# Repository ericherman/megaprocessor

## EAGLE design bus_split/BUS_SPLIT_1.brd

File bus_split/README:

Data bus breakout.

This is just used for generating constant values.

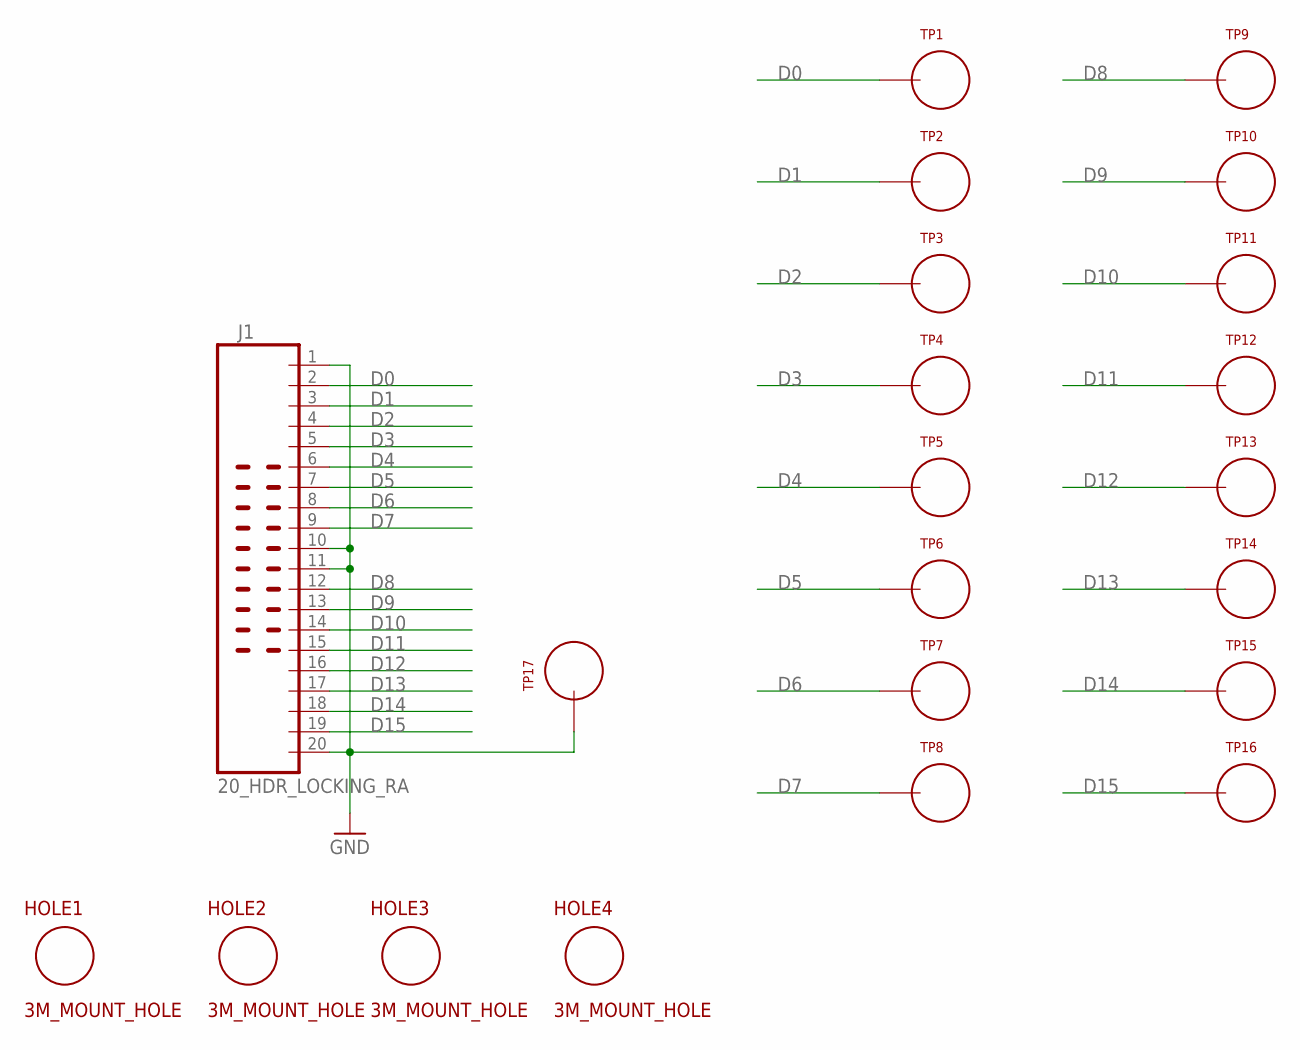
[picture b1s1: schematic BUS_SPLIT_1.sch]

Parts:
HOLE1, HOLE2, HOLE3, HOLE4: 3M_MOUNT_HOLE; 3M_HOLE
J1: 20_HDR_LOCKING_RA
TP1, TP2, TP3, TP4, TP5, TP6, TP7, TP8, TP9, TP10, TP11, TP12, TP13, TP14, TP15, TP16, TP17: TEST_LOOP

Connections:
D0: J1.2, TP1.P$1
D1: J1.3, TP2.P$1
D2: J1.4, TP3.P$1
D3: J1.5, TP4.P$1
D4: J1.6, TP5.P$1
D5: J1.7, TP6.P$1
D6: J1.8, TP7.P$1
D7: J1.9, TP8.P$1
D8: J1.12, TP9.P$1
D9: J1.13, TP10.P$1
D10: J1.14, TP11.P$1
D11: J1.15, TP12.P$1
D12: J1.16, TP13.P$1
D13: J1.17, TP14.P$1
D14: J1.18, TP15.P$1
D15: J1.19, TP16.P$1
GND: J1.1, J1.10, J1.11, J1.20, TP17.P$1

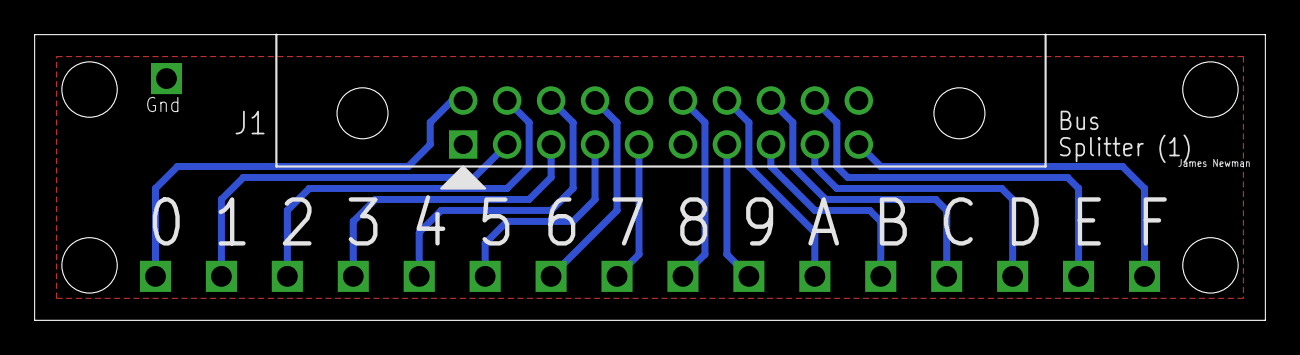
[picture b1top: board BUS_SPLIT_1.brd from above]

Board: 2 copper layers, 71.1 x 16.5 mm, 22 parts (0 on the bottom side), 17 nets.

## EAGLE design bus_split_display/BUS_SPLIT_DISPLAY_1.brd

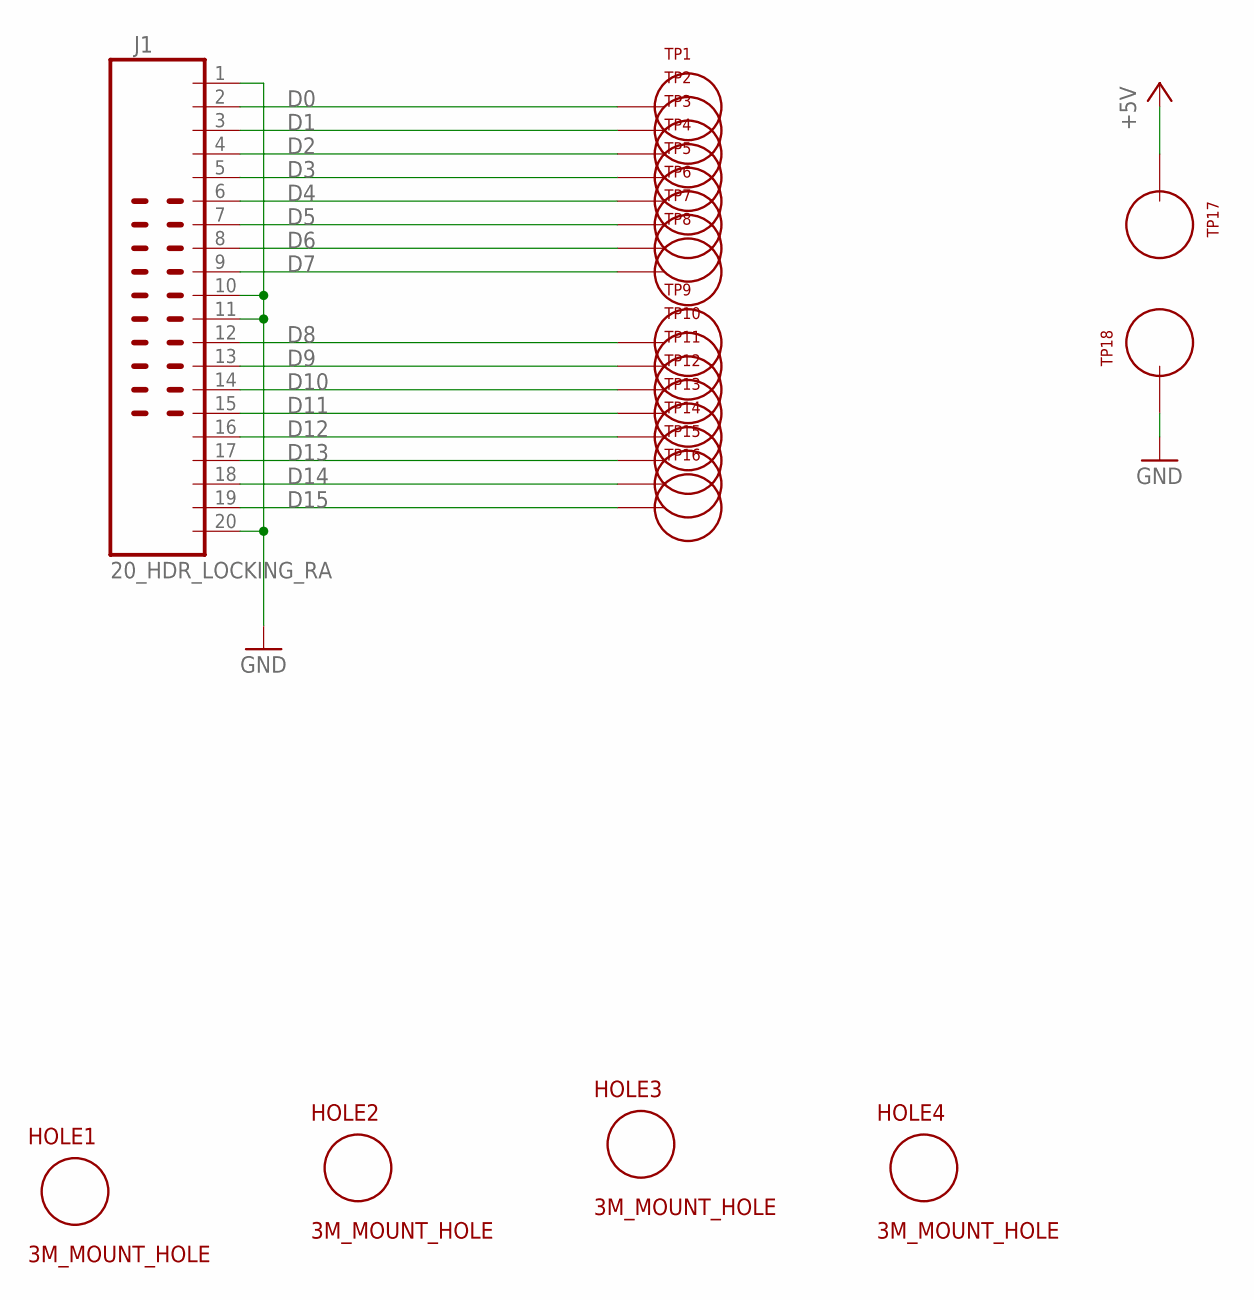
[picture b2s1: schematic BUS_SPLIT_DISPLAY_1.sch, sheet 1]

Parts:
HOLE1, HOLE2, HOLE3, HOLE4: 3M_MOUNT_HOLE; 3M_HOLE
J1: 20_HDR_LOCKING_RA
TP1, TP2, TP3, TP4, TP5, TP6, TP7, TP8, TP9, TP10, TP11, TP12, TP13, TP14, TP15, TP16, TP17, TP18: TEST_LOOP

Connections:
+5V: TP17.P$1; also elsewhere on the board
D0: J1.2, TP1.P$1; also elsewhere on the board
D1: J1.3, TP2.P$1; also elsewhere on the board
D2: J1.4, TP3.P$1; also elsewhere on the board
D3: J1.5, TP4.P$1; also elsewhere on the board
D4: J1.6, TP5.P$1; also elsewhere on the board
D5: J1.7, TP6.P$1; also elsewhere on the board
D6: J1.8, TP7.P$1; also elsewhere on the board
D7: J1.9, TP8.P$1; also elsewhere on the board
D8: J1.12, TP9.P$1; also elsewhere on the board
D9: J1.13, TP10.P$1; also elsewhere on the board
D10: J1.14, TP11.P$1; also elsewhere on the board
D11: J1.15, TP12.P$1; also elsewhere on the board
D12: J1.16, TP13.P$1; also elsewhere on the board
D13: J1.17, TP14.P$1; also elsewhere on the board
D14: J1.18, TP15.P$1; also elsewhere on the board
D15: J1.19, TP16.P$1; also elsewhere on the board
GND: J1.1, J1.10, J1.11, J1.20, TP18.P$1; also elsewhere on the board

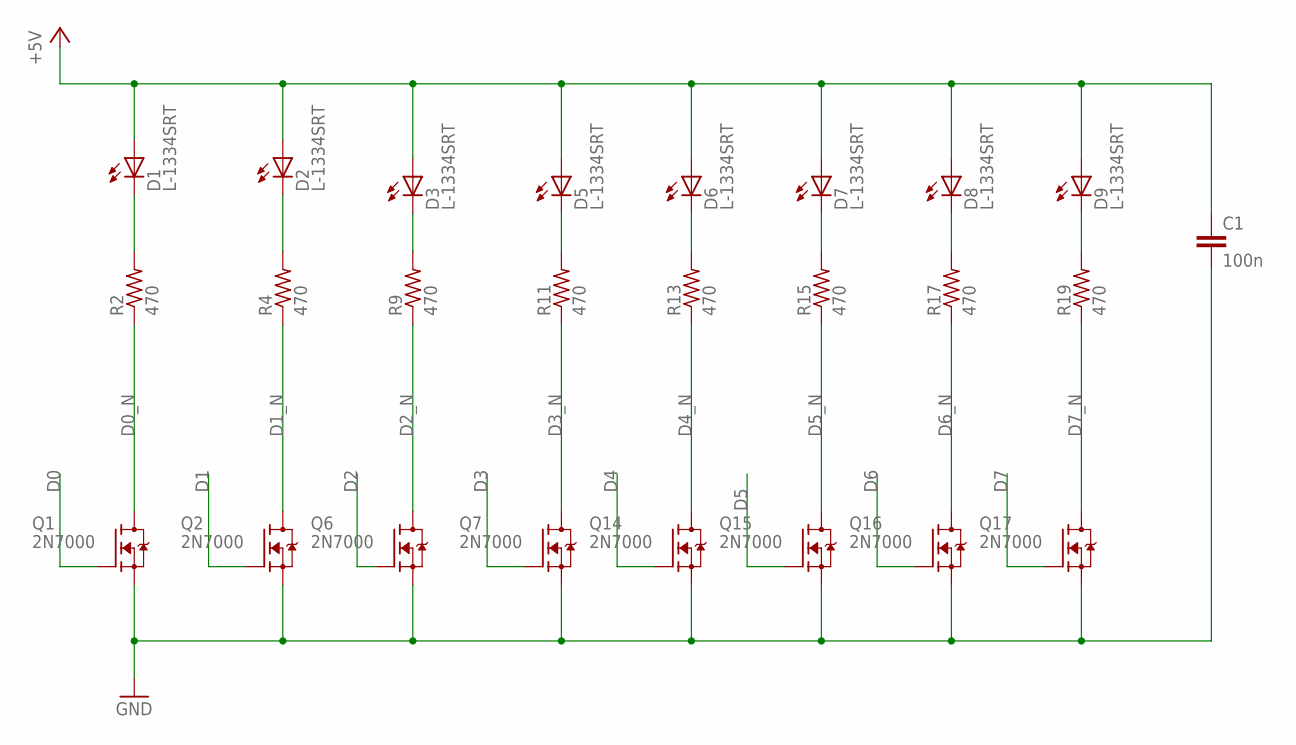
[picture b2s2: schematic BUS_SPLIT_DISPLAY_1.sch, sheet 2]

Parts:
C1: 100n; CAP_P2INCH
D1, D2, D3, D5, D6, D7, D8, D9: L-1334SRT; LED3MM
Q1, Q2, Q6, Q7, Q14, Q15, Q16, Q17: 2N7000; TO92-DGS
R2, R4, R9, R11, R13, R15, R17, R19: 470; R_P2INCH

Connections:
+5V: C1.1, D1.A, D2.A, D3.A, D5.A, D6.A, D7.A, D8.A, D9.A; also elsewhere on the board
D0: Q1.G; also elsewhere on the board
D0_N: Q1.D, R2.1
D1: Q2.G; also elsewhere on the board
D1_N: Q2.D, R4.1
D2: Q6.G; also elsewhere on the board
D2_N: Q6.D, R9.1
D3: Q7.G; also elsewhere on the board
D3_N: Q7.D, R11.1
D4: Q14.G; also elsewhere on the board
D4_N: Q14.D, R13.1
D5: Q15.G; also elsewhere on the board
D5_N: Q15.D, R15.1
D6: Q16.G; also elsewhere on the board
D6_N: Q16.D, R17.1
D7: Q17.G; also elsewhere on the board
D7_N: Q17.D, R19.1
GND: C1.2, Q1.S, Q2.S, Q6.S, Q7.S, Q14.S, Q15.S, Q16.S, Q17.S; also elsewhere on the board
unnamed: D2.K (C), R4.2
unnamed: D1.K (C), R2.2
unnamed: D5.K (C), R11.2
unnamed: D3.K (C), R9.2
unnamed: D6.K (C), R13.2
unnamed: D7.K (C), R15.2
unnamed: D8.K (C), R17.2
unnamed: D9.K (C), R19.2

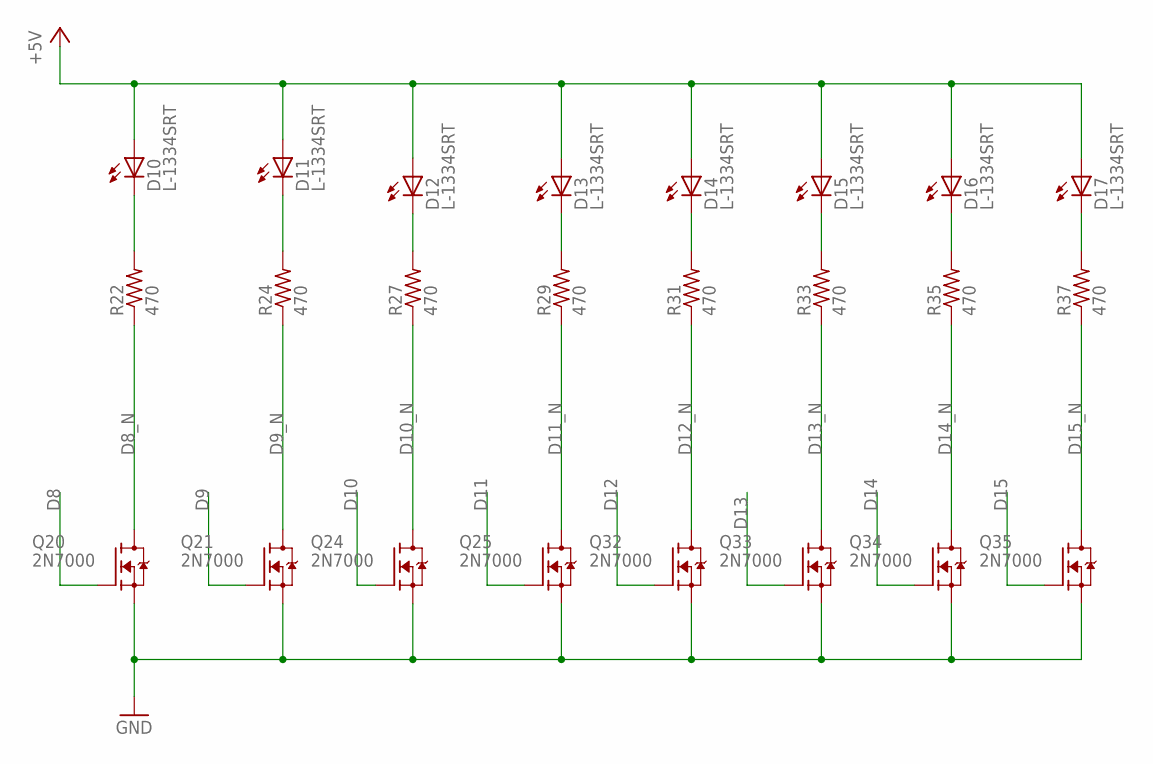
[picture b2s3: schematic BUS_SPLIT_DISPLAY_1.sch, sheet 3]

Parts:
D10, D11, D12, D13, D14, D15, D16, D17: L-1334SRT; LED3MM
Q20, Q21, Q24, Q25, Q32, Q33, Q34, Q35: 2N7000; TO92-DGS
R22, R24, R27, R29, R31, R33, R35, R37: 470; R_P2INCH

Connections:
+5V: D10.A, D11.A, D12.A, D13.A, D14.A, D15.A, D16.A, D17.A; also elsewhere on the board
D8: Q20.G; also elsewhere on the board
D8_N: Q20.D, R22.1
D9: Q21.G; also elsewhere on the board
D9_N: Q21.D, R24.1
D10: Q24.G; also elsewhere on the board
D10_N: Q24.D, R27.1
D11: Q25.G; also elsewhere on the board
D11_N: Q25.D, R29.1
D12: Q32.G; also elsewhere on the board
D12_N: Q32.D, R31.1
D13: Q33.G; also elsewhere on the board
D13_N: Q33.D, R33.1
D14: Q34.G; also elsewhere on the board
D14_N: Q34.D, R35.1
D15: Q35.G; also elsewhere on the board
D15_N: Q35.D, R37.1
GND: Q20.S, Q21.S, Q24.S, Q25.S, Q32.S, Q33.S, Q34.S, Q35.S; also elsewhere on the board
unnamed: D11.K (C), R24.2
unnamed: D10.K (C), R22.2
unnamed: D13.K (C), R29.2
unnamed: D12.K (C), R27.2
unnamed: D14.K (C), R31.2
unnamed: D15.K (C), R33.2
unnamed: D16.K (C), R35.2
unnamed: D17.K (C), R37.2

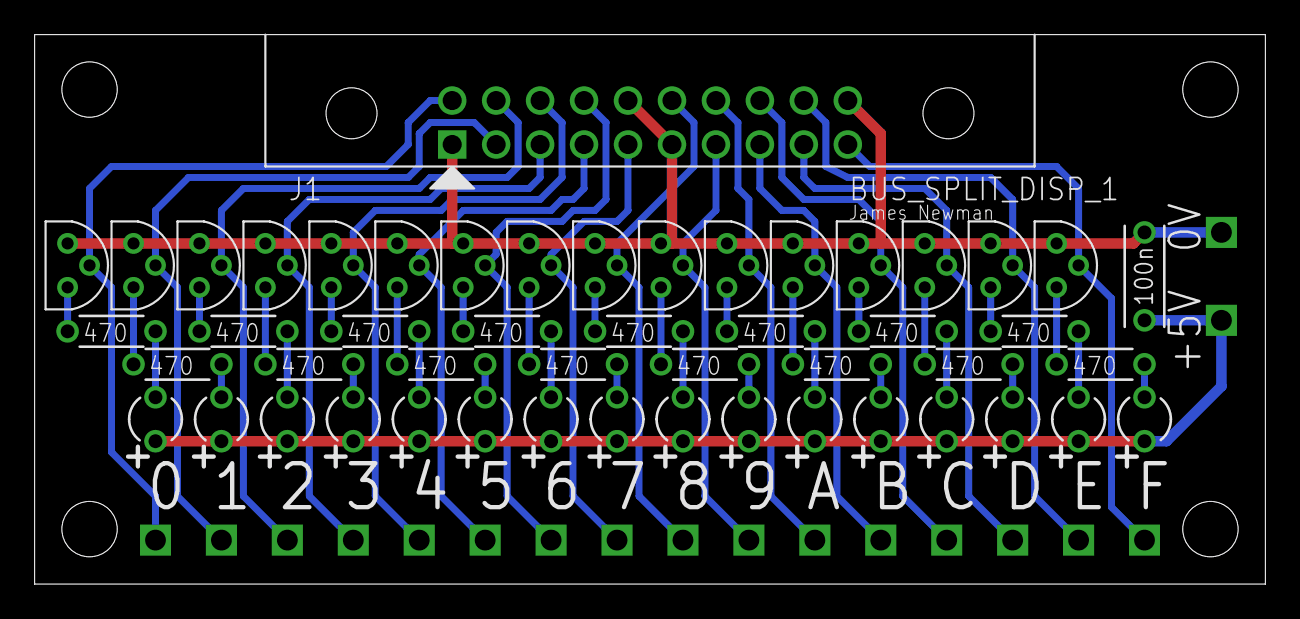
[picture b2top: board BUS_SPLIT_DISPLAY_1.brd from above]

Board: 2 copper layers, 71.1 x 31.8 mm, 72 parts (0 on the bottom side), 50 nets.

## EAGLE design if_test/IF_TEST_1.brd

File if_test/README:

Test Board

To test the larger scale structures I need a huge amount of I/O out of
the PC so I built an I/O expander. These can be daisy chained (I hope,
not tried it yet) to give me what I need to test the largest modules.
Made a stupid stupid mistake on the pinout for the very simplest chip.
Hence the carbuncle.

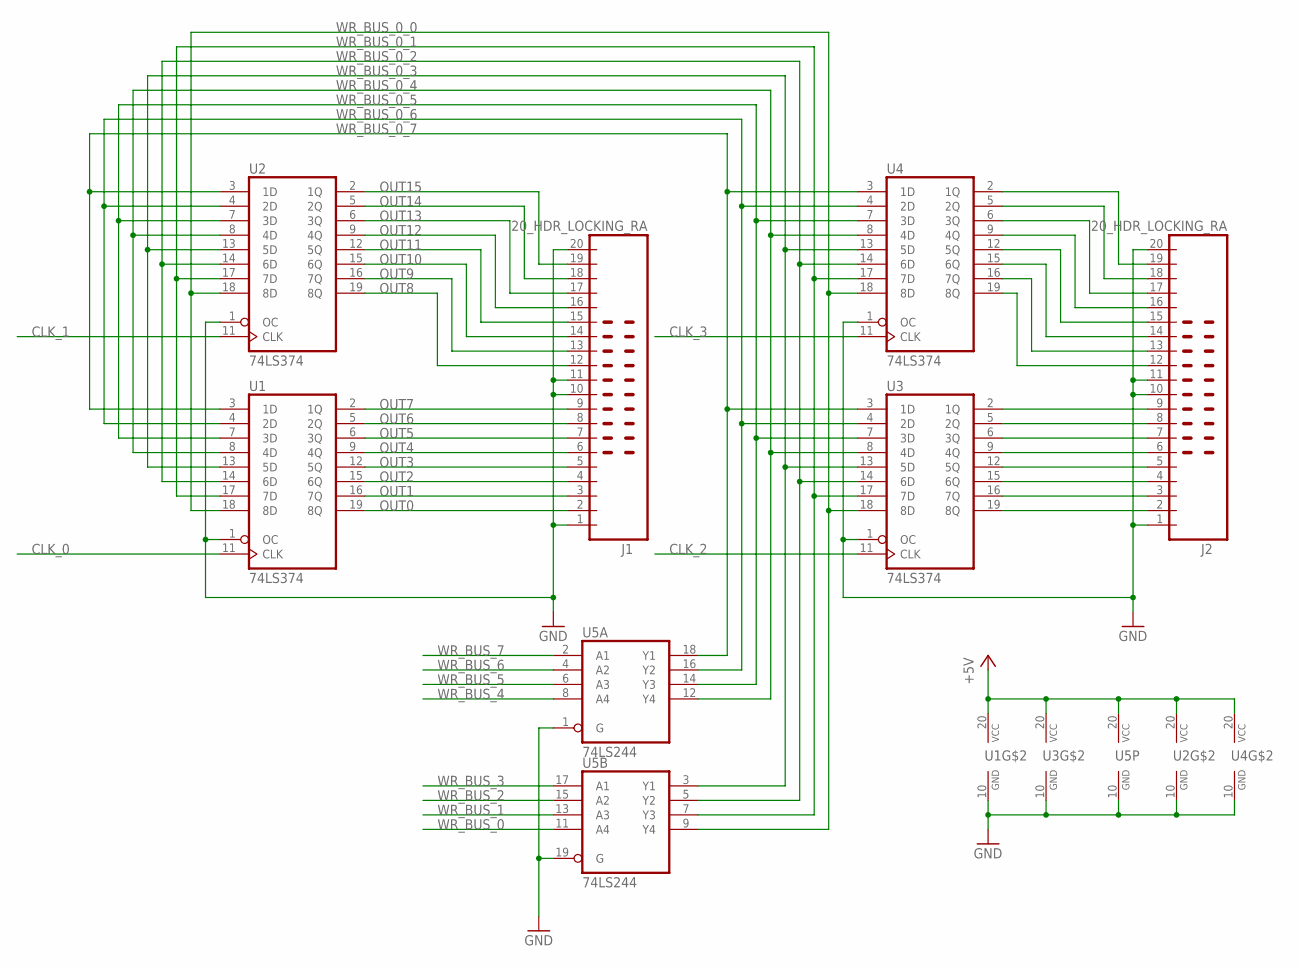
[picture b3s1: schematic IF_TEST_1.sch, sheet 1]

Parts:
J1, J2: 20_HDR_LOCKING_RA
U1, U2, U3, U4: 74LS374; DIP20
U5: 74LS244; DIP20

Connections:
+5V: U1.20 (VCC), U2.20 (VCC), U3.20 (VCC), U4.20 (VCC), U5.20 (VCC); also elsewhere on the board
CLK_0: U1.11 (CLK); also elsewhere on the board
CLK_1: U2.11 (CLK); also elsewhere on the board
CLK_2: U3.11 (CLK); also elsewhere on the board
CLK_3: U4.11 (CLK); also elsewhere on the board
GND: J1.1, J1.10, J1.11, J1.20, J2.1, J2.10, J2.11, J2.20, U1.1 (OC), U1.10 (GND), U2.1 (OC), U2.10 (GND), U3.1 (OC), U3.10 (GND), U4.1 (OC), U4.10 (GND), U5.1 (G), U5.10 (GND), U5.19 (G); also elsewhere on the board
unnamed: J2.2, U3.19 (8Q)
unnamed: J2.3, U3.16 (7Q)
unnamed: J2.4, U3.15 (6Q)
unnamed: J2.5, U3.12 (5Q)
unnamed: J2.6, U3.9 (4Q)
unnamed: J2.7, U3.6 (3Q)
unnamed: J2.8, U3.5 (2Q)
unnamed: J2.9, U3.2 (1Q)
unnamed: J2.12, U4.19 (8Q)
unnamed: J2.13, U4.16 (7Q)
unnamed: J2.14, U4.15 (6Q)
unnamed: J2.15, U4.12 (5Q)
unnamed: J2.16, U4.9 (4Q)
unnamed: J2.17, U4.6 (3Q)
unnamed: J2.18, U4.5 (2Q)
unnamed: J2.19, U4.2 (1Q)
OUT0: J1.2, U1.19 (8Q)
OUT1: J1.3, U1.16 (7Q)
OUT2: J1.4, U1.15 (6Q)
OUT3: J1.5, U1.12 (5Q)
OUT4: J1.6, U1.9 (4Q)
OUT5: J1.7, U1.6 (3Q)
OUT6: J1.8, U1.5 (2Q)
OUT7: J1.9, U1.2 (1Q)
OUT8: J1.12, U2.19 (8Q)
OUT9: J1.13, U2.16 (7Q)
OUT10: J1.14, U2.15 (6Q)
OUT11: J1.15, U2.12 (5Q)
OUT12: J1.16, U2.9 (4Q)
OUT13: J1.17, U2.6 (3Q)
OUT14: J1.18, U2.5 (2Q)
OUT15: J1.19, U2.2 (1Q)
WR_BUS_0: U5.11 (A4); also elsewhere on the board
WR_BUS_0_0: U1.18 (8D), U2.18 (8D), U3.18 (8D), U4.18 (8D), U5.9 (Y4); also elsewhere on the board
WR_BUS_0_1: U1.17 (7D), U2.17 (7D), U3.17 (7D), U4.17 (7D), U5.7 (Y3); also elsewhere on the board
WR_BUS_0_2: U1.14 (6D), U2.14 (6D), U3.14 (6D), U4.14 (6D), U5.5 (Y2); also elsewhere on the board
WR_BUS_0_3: U1.13 (5D), U2.13 (5D), U3.13 (5D), U4.13 (5D), U5.3 (Y1); also elsewhere on the board
WR_BUS_0_4: U1.8 (4D), U2.8 (4D), U3.8 (4D), U4.8 (4D), U5.12 (Y4); also elsewhere on the board
WR_BUS_0_5: U1.7 (3D), U2.7 (3D), U3.7 (3D), U4.7 (3D), U5.14 (Y3); also elsewhere on the board
WR_BUS_0_6: U1.4 (2D), U2.4 (2D), U3.4 (2D), U4.4 (2D), U5.16 (Y2); also elsewhere on the board
WR_BUS_0_7: U1.3 (1D), U2.3 (1D), U3.3 (1D), U4.3 (1D), U5.18 (Y1); also elsewhere on the board
WR_BUS_1: U5.13 (A3); also elsewhere on the board
WR_BUS_2: U5.15 (A2); also elsewhere on the board
WR_BUS_3: U5.17 (A1); also elsewhere on the board
WR_BUS_4: U5.8 (A4); also elsewhere on the board
WR_BUS_5: U5.6 (A3); also elsewhere on the board
WR_BUS_6: U5.4 (A2); also elsewhere on the board
WR_BUS_7: U5.2 (A1); also elsewhere on the board

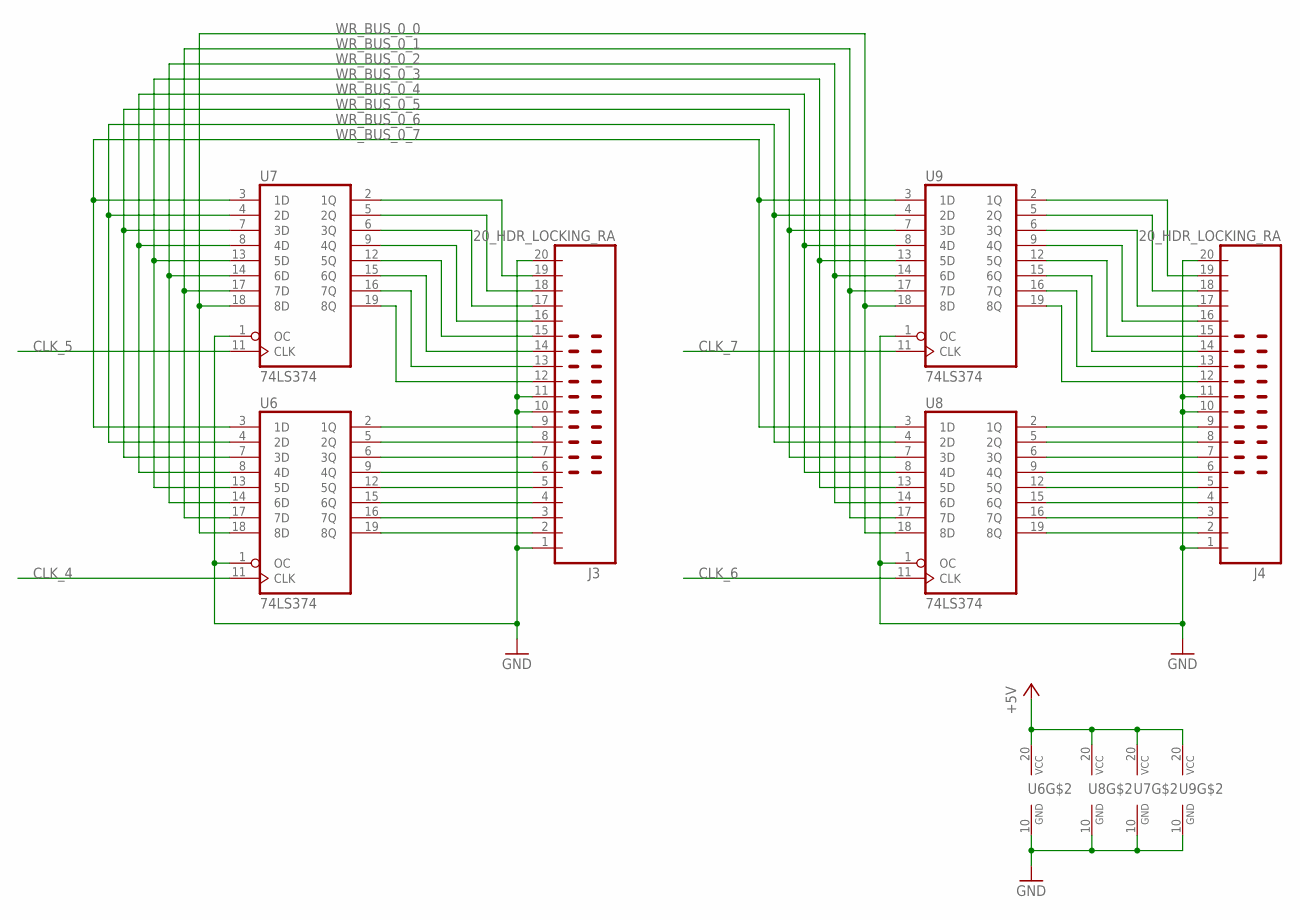
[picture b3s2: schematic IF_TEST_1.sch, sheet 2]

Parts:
J3, J4: 20_HDR_LOCKING_RA
U6, U7, U8, U9: 74LS374; DIP20

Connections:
+5V: U6.20 (VCC), U7.20 (VCC), U8.20 (VCC), U9.20 (VCC); also elsewhere on the board
CLK_4: U6.11 (CLK); also elsewhere on the board
CLK_5: U7.11 (CLK); also elsewhere on the board
CLK_6: U8.11 (CLK); also elsewhere on the board
CLK_7: U9.11 (CLK); also elsewhere on the board
GND: J3.1, J3.10, J3.11, J3.20, J4.1, J4.10, J4.11, J4.20, U6.1 (OC), U6.10 (GND), U7.1 (OC), U7.10 (GND), U8.1 (OC), U8.10 (GND), U9.1 (OC), U9.10 (GND); also elsewhere on the board
unnamed: J3.2, U6.19 (8Q)
unnamed: J3.3, U6.16 (7Q)
unnamed: J3.4, U6.15 (6Q)
unnamed: J3.5, U6.12 (5Q)
unnamed: J3.6, U6.9 (4Q)
unnamed: J3.7, U6.6 (3Q)
unnamed: J3.8, U6.5 (2Q)
unnamed: J3.9, U6.2 (1Q)
unnamed: J3.12, U7.19 (8Q)
unnamed: J3.13, U7.16 (7Q)
unnamed: J3.14, U7.15 (6Q)
unnamed: J3.15, U7.12 (5Q)
unnamed: J3.16, U7.9 (4Q)
unnamed: J3.17, U7.6 (3Q)
unnamed: J3.18, U7.5 (2Q)
unnamed: J3.19, U7.2 (1Q)
unnamed: J4.2, U8.19 (8Q)
unnamed: J4.3, U8.16 (7Q)
unnamed: J4.4, U8.15 (6Q)
unnamed: J4.5, U8.12 (5Q)
unnamed: J4.6, U8.9 (4Q)
unnamed: J4.7, U8.6 (3Q)
unnamed: J4.8, U8.5 (2Q)
unnamed: J4.9, U8.2 (1Q)
unnamed: J4.12, U9.19 (8Q)
unnamed: J4.13, U9.16 (7Q)
unnamed: J4.14, U9.15 (6Q)
unnamed: J4.15, U9.12 (5Q)
unnamed: J4.16, U9.9 (4Q)
unnamed: J4.17, U9.6 (3Q)
unnamed: J4.18, U9.5 (2Q)
unnamed: J4.19, U9.2 (1Q)
WR_BUS_0_0: U6.18 (8D), U7.18 (8D), U8.18 (8D), U9.18 (8D); also elsewhere on the board
WR_BUS_0_1: U6.17 (7D), U7.17 (7D), U8.17 (7D), U9.17 (7D); also elsewhere on the board
WR_BUS_0_2: U6.14 (6D), U7.14 (6D), U8.14 (6D), U9.14 (6D); also elsewhere on the board
WR_BUS_0_3: U6.13 (5D), U7.13 (5D), U8.13 (5D), U9.13 (5D); also elsewhere on the board
WR_BUS_0_4: U6.8 (4D), U7.8 (4D), U8.8 (4D), U9.8 (4D); also elsewhere on the board
WR_BUS_0_5: U6.7 (3D), U7.7 (3D), U8.7 (3D), U9.7 (3D); also elsewhere on the board
WR_BUS_0_6: U6.4 (2D), U7.4 (2D), U8.4 (2D), U9.4 (2D); also elsewhere on the board
WR_BUS_0_7: U6.3 (1D), U7.3 (1D), U8.3 (1D), U9.3 (1D); also elsewhere on the board

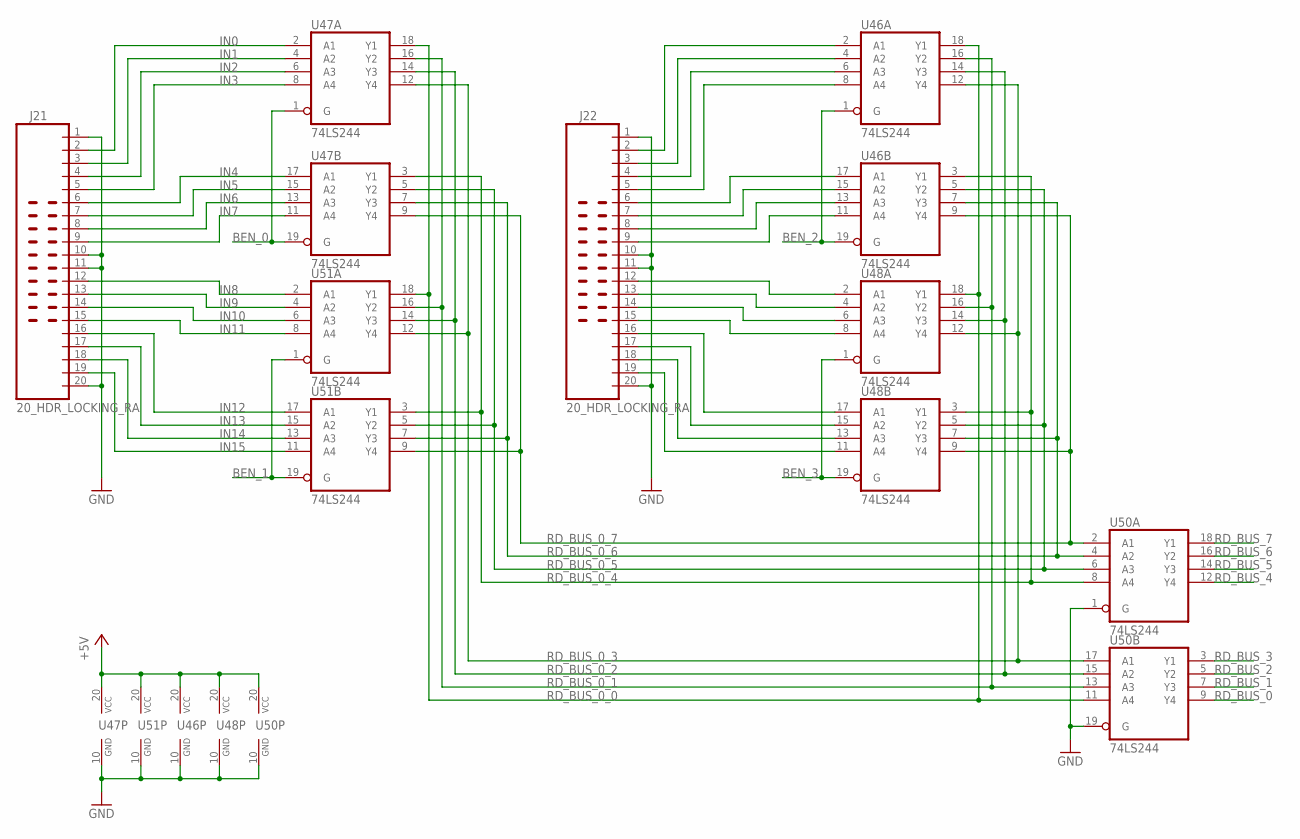
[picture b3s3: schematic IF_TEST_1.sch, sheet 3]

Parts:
J21, J22: 20_HDR_LOCKING_RA
U46, U47, U48, U50, U51: 74LS244; DIP20

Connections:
+5V: U46.20 (VCC), U47.20 (VCC), U48.20 (VCC), U50.20 (VCC), U51.20 (VCC); also elsewhere on the board
BEN_0: U47.1 (G), U47.19 (G); also elsewhere on the board
BEN_1: U51.1 (G), U51.19 (G); also elsewhere on the board
BEN_2: U46.1 (G), U46.19 (G); also elsewhere on the board
BEN_3: U48.1 (G), U48.19 (G); also elsewhere on the board
GND: J21.1, J21.10, J21.11, J21.20, J22.1, J22.10, J22.11, J22.20, U46.10 (GND), U47.10 (GND), U48.10 (GND), U50.1 (G), U50.10 (GND), U50.19 (G), U51.10 (GND); also elsewhere on the board
IN0: J21.2, U47.2 (A1)
IN1: J21.3, U47.4 (A2)
IN2: J21.4, U47.6 (A3)
IN3: J21.5, U47.8 (A4)
IN4: J21.6, U47.17 (A1)
IN5: J21.7, U47.15 (A2)
IN6: J21.8, U47.13 (A3)
IN7: J21.9, U47.11 (A4)
IN8: J21.12, U51.2 (A1)
IN9: J21.13, U51.4 (A2)
IN10: J21.14, U51.6 (A3)
IN11: J21.15, U51.8 (A4)
IN12: J21.16, U51.17 (A1)
IN13: J21.17, U51.15 (A2)
IN14: J21.18, U51.13 (A3)
IN15: J21.19, U51.11 (A4)
unnamed: J22.2, U46.2 (A1)
unnamed: J22.3, U46.4 (A2)
unnamed: J22.4, U46.6 (A3)
unnamed: J22.5, U46.8 (A4)
unnamed: J22.6, U46.17 (A1)
unnamed: J22.7, U46.15 (A2)
unnamed: J22.8, U46.13 (A3)
unnamed: J22.9, U46.11 (A4)
unnamed: J22.12, U48.2 (A1)
unnamed: J22.13, U48.4 (A2)
unnamed: J22.14, U48.6 (A3)
unnamed: J22.15, U48.8 (A4)
unnamed: J22.19, U48.11 (A4)
unnamed: J22.18, U48.13 (A3)
unnamed: J22.17, U48.15 (A2)
unnamed: J22.16, U48.17 (A1)
RD_BUS_0: U50.9 (Y4); also elsewhere on the board
RD_BUS_0_0: U46.18 (Y1), U47.18 (Y1), U48.18 (Y1), U50.11 (A4), U51.18 (Y1); also elsewhere on the board
RD_BUS_0_1: U46.16 (Y2), U47.16 (Y2), U48.16 (Y2), U50.13 (A3), U51.16 (Y2); also elsewhere on the board
RD_BUS_0_2: U46.14 (Y3), U47.14 (Y3), U48.14 (Y3), U50.15 (A2), U51.14 (Y3); also elsewhere on the board
RD_BUS_0_3: U46.12 (Y4), U47.12 (Y4), U48.12 (Y4), U50.17 (A1), U51.12 (Y4); also elsewhere on the board
RD_BUS_0_4: U46.3 (Y1), U47.3 (Y1), U48.3 (Y1), U50.8 (A4), U51.3 (Y1); also elsewhere on the board
RD_BUS_0_5: U46.5 (Y2), U47.5 (Y2), U48.5 (Y2), U50.6 (A3), U51.5 (Y2); also elsewhere on the board
RD_BUS_0_6: U46.7 (Y3), U47.7 (Y3), U48.7 (Y3), U50.4 (A2), U51.7 (Y3); also elsewhere on the board
RD_BUS_0_7: U46.9 (Y4), U47.9 (Y4), U48.9 (Y4), U50.2 (A1), U51.9 (Y4); also elsewhere on the board
RD_BUS_1: U50.7 (Y3); also elsewhere on the board
RD_BUS_2: U50.5 (Y2); also elsewhere on the board
RD_BUS_3: U50.3 (Y1); also elsewhere on the board
RD_BUS_4: U50.12 (Y4); also elsewhere on the board
RD_BUS_5: U50.14 (Y3); also elsewhere on the board
RD_BUS_6: U50.16 (Y2); also elsewhere on the board
RD_BUS_7: U50.18 (Y1); also elsewhere on the board

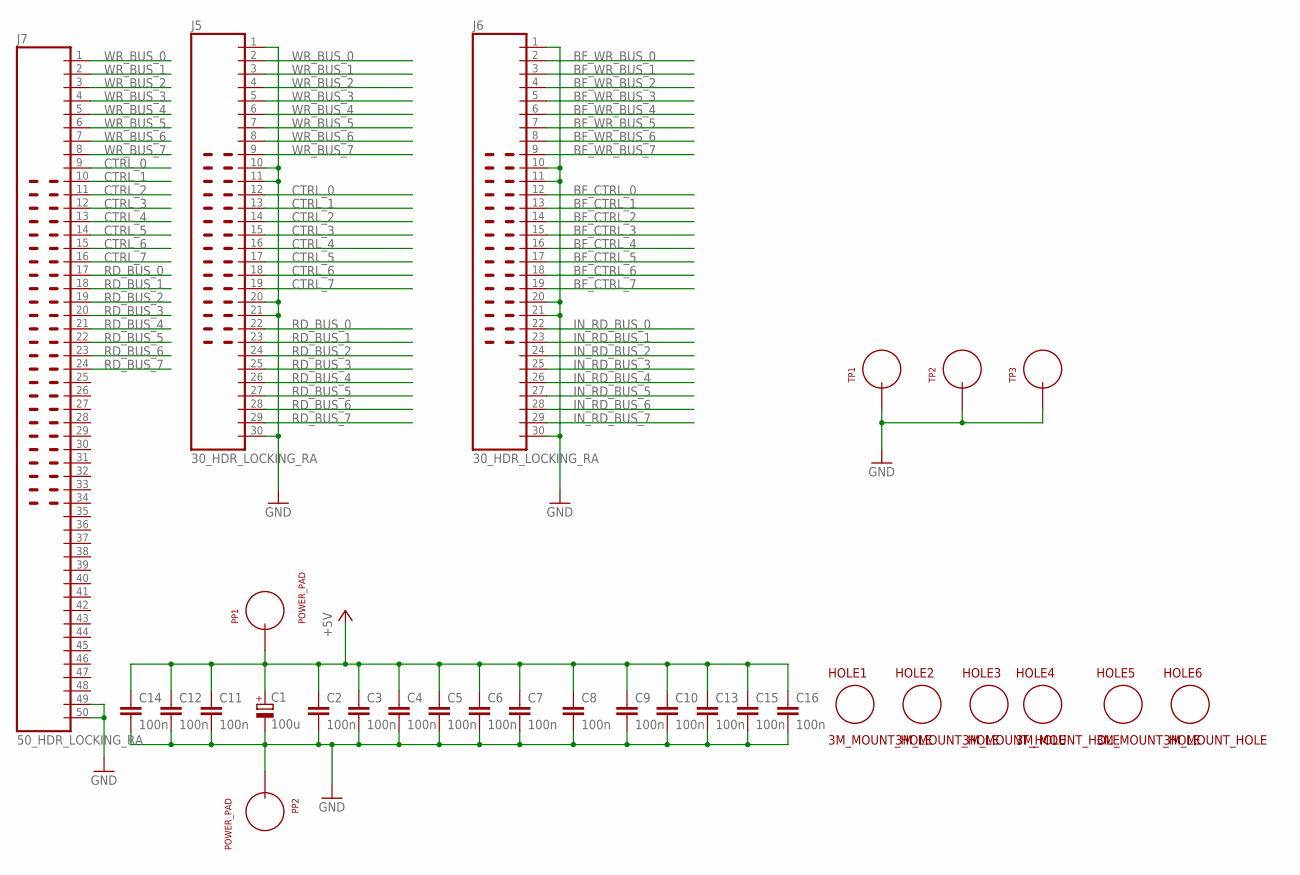
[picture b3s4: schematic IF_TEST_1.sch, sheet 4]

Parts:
C1: 100u; POLARISED_CAP_2P5_6P3MM
C2, C3, C4, C5, C6, C7, C8, C9, C10, C11, C12, C13, C14, C15, C16: 100n; CAP_P2INCH
HOLE1, HOLE2, HOLE3, HOLE4, HOLE5, HOLE6: 3M_MOUNT_HOLE; 3M_HOLE
J5, J6: 30_HDR_LOCKING_RA
J7: 50_HDR_LOCKING_RA
PP1, PP2: POWER_PAD
TP1, TP2, TP3: TEST_LOOP

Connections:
+5V: C1.A, C2.1, C3.1, C4.1, C5.1, C6.1, C7.1, C8.1, C9.1, C10.1, C11.1, C12.1, C13.1, C14.1, C15.1, C16.1, PP1.1; also elsewhere on the board
BF_CTRL_0: J6.12; also elsewhere on the board
BF_CTRL_1: J6.13; also elsewhere on the board
BF_CTRL_2: J6.14; also elsewhere on the board
BF_CTRL_3: J6.15; also elsewhere on the board
BF_CTRL_4: J6.16; also elsewhere on the board
BF_CTRL_5: J6.17; also elsewhere on the board
BF_CTRL_6: J6.18; also elsewhere on the board
BF_CTRL_7: J6.19; also elsewhere on the board
BF_WR_BUS_0: J6.2; also elsewhere on the board
BF_WR_BUS_1: J6.3; also elsewhere on the board
BF_WR_BUS_2: J6.4; also elsewhere on the board
BF_WR_BUS_3: J6.5; also elsewhere on the board
BF_WR_BUS_4: J6.6; also elsewhere on the board
BF_WR_BUS_5: J6.7; also elsewhere on the board
BF_WR_BUS_6: J6.8; also elsewhere on the board
BF_WR_BUS_7: J6.9; also elsewhere on the board
CTRL_0: J5.12, J7.9; also elsewhere on the board
CTRL_1: J5.13, J7.10; also elsewhere on the board
CTRL_2: J5.14, J7.11; also elsewhere on the board
CTRL_3: J5.15, J7.12; also elsewhere on the board
CTRL_4: J5.16, J7.13; also elsewhere on the board
CTRL_5: J5.17, J7.14; also elsewhere on the board
CTRL_6: J5.18, J7.15; also elsewhere on the board
CTRL_7: J5.19, J7.16; also elsewhere on the board
GND: C1.K, C2.2, C3.2, C4.2, C5.2, C6.2, C7.2, C8.2, C9.2, C10.2, C11.2, C12.2, C13.2, C14.2, C15.2, C16.2, J5.1, J5.10, J5.11, J5.20, J5.21, J5.30, J6.1, J6.10, J6.11, J6.20, J6.21, J6.30, J7.49, J7.50, PP2.1, TP1.P$1, TP2.P$1, TP3.P$1; also elsewhere on the board
IN_RD_BUS_0: J6.22; also elsewhere on the board
IN_RD_BUS_1: J6.23; also elsewhere on the board
IN_RD_BUS_2: J6.24; also elsewhere on the board
IN_RD_BUS_3: J6.25; also elsewhere on the board
IN_RD_BUS_4: J6.26; also elsewhere on the board
IN_RD_BUS_5: J6.27; also elsewhere on the board
IN_RD_BUS_6: J6.28; also elsewhere on the board
IN_RD_BUS_7: J6.29; also elsewhere on the board
RD_BUS_0: J5.22, J7.17; also elsewhere on the board
RD_BUS_1: J5.23, J7.18; also elsewhere on the board
RD_BUS_2: J5.24, J7.19; also elsewhere on the board
RD_BUS_3: J5.25, J7.20; also elsewhere on the board
RD_BUS_4: J5.26, J7.21; also elsewhere on the board
RD_BUS_5: J5.27, J7.22; also elsewhere on the board
RD_BUS_6: J5.28, J7.23; also elsewhere on the board
RD_BUS_7: J5.29, J7.24; also elsewhere on the board
WR_BUS_0: J5.2, J7.1; also elsewhere on the board
WR_BUS_1: J5.3, J7.2; also elsewhere on the board
WR_BUS_2: J5.4, J7.3; also elsewhere on the board
WR_BUS_3: J5.5, J7.4; also elsewhere on the board
WR_BUS_4: J5.6, J7.5; also elsewhere on the board
WR_BUS_5: J5.7, J7.6; also elsewhere on the board
WR_BUS_6: J5.8, J7.7; also elsewhere on the board
WR_BUS_7: J5.9, J7.8; also elsewhere on the board

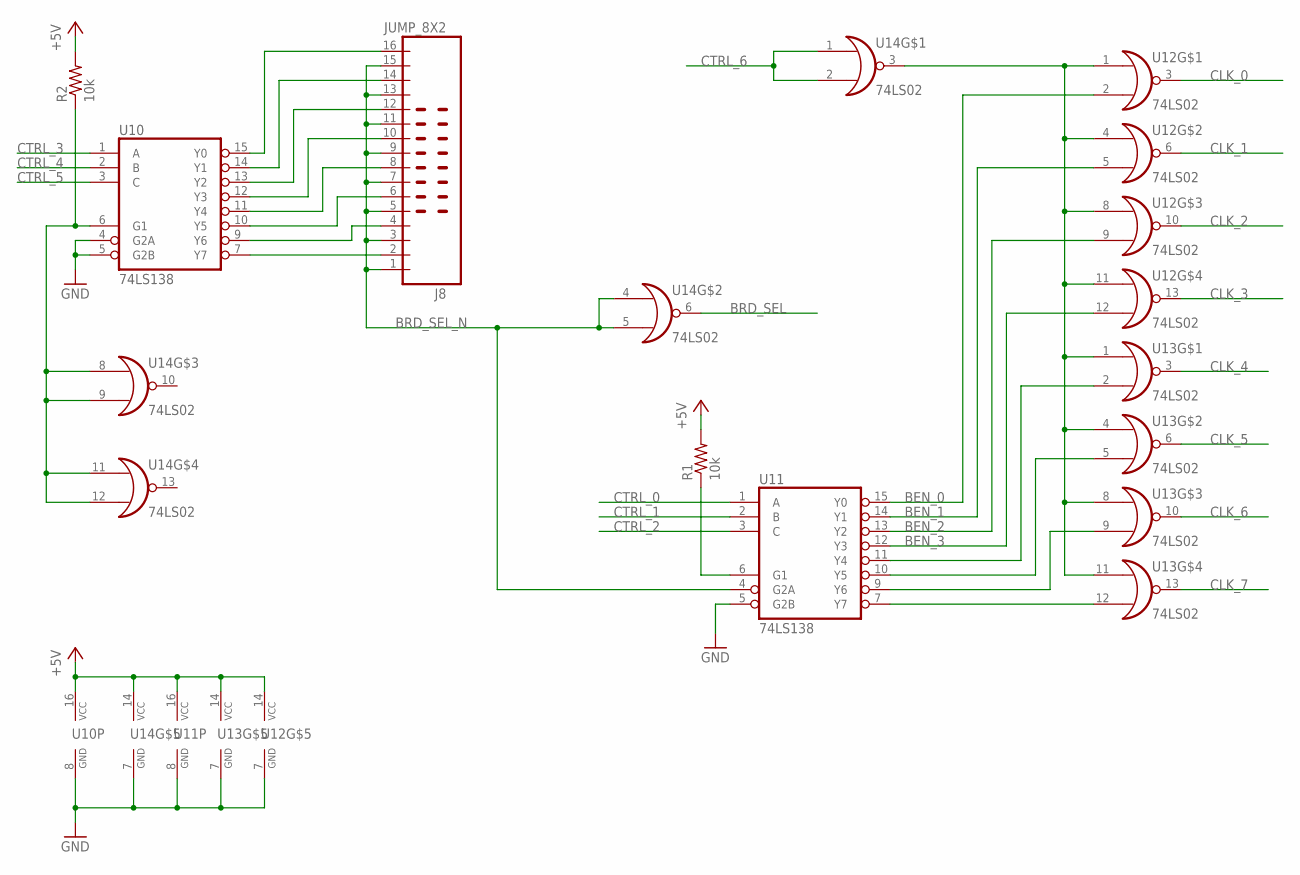
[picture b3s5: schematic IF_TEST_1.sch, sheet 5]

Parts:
J8: JUMP_8X2
R1, R2: 10k; R_P2INCH
U10, U11: 74LS138; DIP16
U12, U13, U14: 74LS02; DIP14

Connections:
+5V: R1.2, R2.2, U10.16 (VCC), U11.16 (VCC), U12.14 (VCC), U13.14 (VCC), U14.14 (VCC); also elsewhere on the board
BEN_0: U11.15 (Y0), U12.2 (I1); also elsewhere on the board
BEN_1: U11.14 (Y1), U12.5 (I1); also elsewhere on the board
BEN_2: U11.13 (Y2), U12.9 (I1); also elsewhere on the board
BEN_3: U11.12 (Y3), U12.12 (I1); also elsewhere on the board
BRD_SEL: U14.6 (O); also elsewhere on the board
BRD_SEL_N: J8.1, J8.3, J8.5, J8.7, J8.9, J8.11, J8.13, J8.15, U11.4 (G2A), U14.4 (I0), U14.5 (I1)
CLK_0: U12.3 (O); also elsewhere on the board
CLK_1: U12.6 (O); also elsewhere on the board
CLK_2: U12.10 (O); also elsewhere on the board
CLK_3: U12.13 (O); also elsewhere on the board
CLK_4: U13.3 (O); also elsewhere on the board
CLK_5: U13.6 (O); also elsewhere on the board
CLK_6: U13.10 (O); also elsewhere on the board
CLK_7: U13.13 (O); also elsewhere on the board
CTRL_0: U11.1 (A); also elsewhere on the board
CTRL_1: U11.2 (B); also elsewhere on the board
CTRL_2: U11.3 (C); also elsewhere on the board
CTRL_3: U10.1 (A); also elsewhere on the board
CTRL_4: U10.2 (B); also elsewhere on the board
CTRL_5: U10.3 (C); also elsewhere on the board
CTRL_6: U14.1 (I0), U14.2 (I1); also elsewhere on the board
GND: U10.4 (G2A), U10.5 (G2B), U10.8 (GND), U11.5 (G2B), U11.8 (GND), U12.7 (GND), U13.7 (GND), U14.7 (GND); also elsewhere on the board
unnamed: J8.2, U10.7 (Y7)
unnamed: J8.4, U10.9 (Y6)
unnamed: J8.6, U10.10 (Y5)
unnamed: J8.8, U10.11 (Y4)
unnamed: J8.10, U10.12 (Y3)
unnamed: J8.12, U10.13 (Y2)
unnamed: J8.14, U10.14 (Y1)
unnamed: J8.16, U10.15 (Y0)
unnamed: R2.1, U10.6 (G1), U14.8 (I0), U14.9 (I1), U14.11 (I0), U14.12 (I1)
unnamed: U12.1 (I0), U12.4 (I0), U12.8 (I0), U12.11 (I0), U13.1 (I0), U13.4 (I0), U13.8 (I0), U13.11 (I0), U14.3 (O)
unnamed: U11.7 (Y7), U13.12 (I1)
unnamed: U11.9 (Y6), U13.9 (I1)
unnamed: U11.10 (Y5), U13.5 (I1)
unnamed: U11.11 (Y4), U13.2 (I1)
unnamed: R1.1, U11.6 (G1)
